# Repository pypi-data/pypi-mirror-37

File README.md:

# PyPI code 37

This repo contains 40000 packages uploaded to PyPI between 
2018-10-08 14:18 and 2018-11-02 07:18.

The repo is 100% (40000/40000) complete.

Package contents can be found [in the code branch](https://github.com/pypi-data/pypi-mirror-37/tree/code/packages).

A browsable package list for all repositories [all packages here](https://pypi-data.github.io/website/repositories/pypi-mirror-37).

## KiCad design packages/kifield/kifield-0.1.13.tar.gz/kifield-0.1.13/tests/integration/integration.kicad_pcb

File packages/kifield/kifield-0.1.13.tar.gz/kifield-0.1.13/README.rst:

===============================
kifield
===============================

.. image:: https://img.shields.io/pypi/v/kifield.svg
        :target: https://pypi.python.org/pypi/kifield
.. image:: https://travis-ci.org/xesscorp/KiField.svg?branch=master
    :target: https://travis-ci.org/xesscorp/KiField

A utility for manipulating part fields in KiCad schematic files or libraries.
KiField can extract all the component fields from a schematic or library
and place them into a spreadsheet for bulk editing, after which you can insert the
edited values from the spreadsheet back into the schematic or library.

KiField is usually employed in a three-step process:

#. First use KiField to extract the part field labels and values from a
   schematic or library and place them into a CSV or XLSX spreadsheet file.

#. Edit the spreadsheet file to change existing field values, add entirely
   new fields, or completely delete fields.

#. Finally, use KiField to insert the updated field labels and values from
   the spreadsheet file into the schematic or library.

* Free software: MIT license
* Documentation: https://xesscorp.github.io/KiField.

Features
--------

* Extracts all fields and values from one or more KiCad schematic libraries or files
  (even hierarchical designs), and inserts them into a spreadsheet (either
  CSV or XLSX format).
* Extracts all fields and values from one or more CSV or XLSX spreadsheet files
  and inserts them into one or more KiCad schematics or libraries.

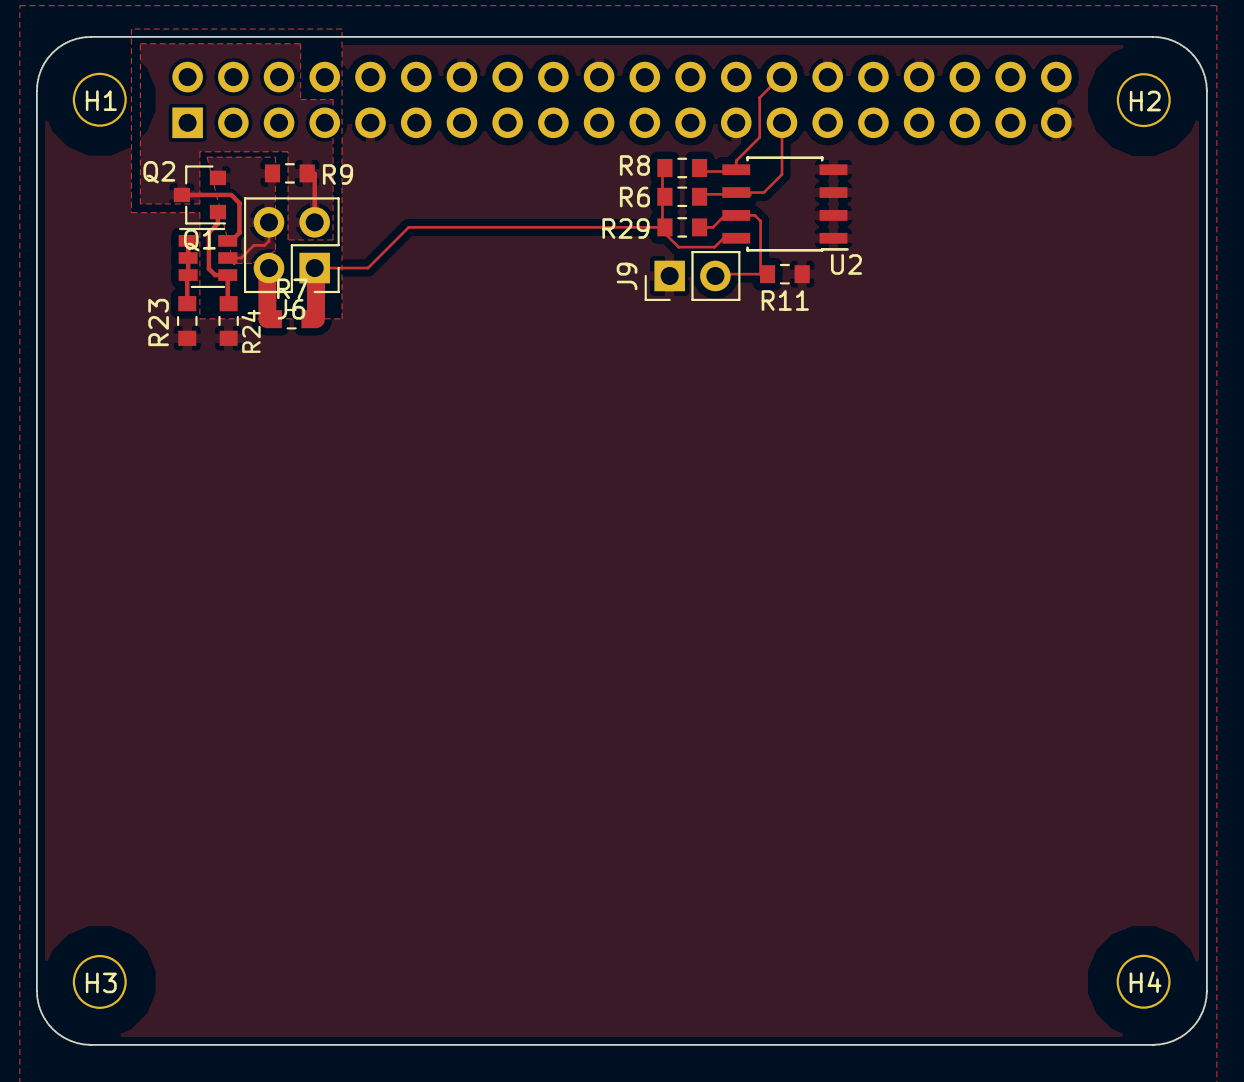
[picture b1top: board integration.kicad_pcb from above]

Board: 4 copper layers, 65.0 x 56.0 mm, 18 parts (1 on the bottom side), 10 nets.

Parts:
H1, H2, H3, H4: 3mm_Mounting_Hole; NPTH_3mm_ID
J3: 40HAT; PinSocket_2x20_P2.54mm_Vertical
J6: CONN_02X02; PinHeader_2x02_P2.54mm_Vertical
J9: CONN_01X02; PinHeader_1x02_P2.54mm_Vertical
Q1: DMG2305UX; SOT-23
Q2: DMMT5401; SOT-23-6
R6, R8: 3.9K; R_0603_1608Metric_Pad0.84x1.00mm_HandSolder
R7, R9, R11: DNP; R_0603_1608Metric_Pad0.84x1.00mm_HandSolder
R23, R24: 22; R_0603_1608Metric_Pad0.84x1.00mm_HandSolder
R29: 10K; R_0603_1608Metric_Pad0.84x1.00mm_HandSolder
U2: CAT24C32; SOIC-8_3.9x4.9mm_P1.27mm

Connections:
/ID_SC_EEPROM: J3.28, R8.2, U2.5
/ID_SD_EEPROM: J3.27, R6.2, U2.6
/P3V3: J6.1, R6.1, R7.2, R8.1, R29.1, U2.8
/P3V3_HAT: J3.1, J6.2, R7.1
/P5V: J6.3, Q1.3, Q2.6, R9.2
/P5V_HAT: J3.2, J3.4, J6.4, Q1.2, Q2.5, R9.1
GND: J3.6, J3.9, J3.14, J3.20, J3.25, J3.30, J3.34, J3.39, J9.1, R11.2, R23.2, R24.2, U2.1, U2.2, U2.3, U2.4
unnamed: J9.2, R11.1, R29.2, U2.7
unnamed: Q1.1, Q2.4, R24.1
unnamed: Q2.1, Q2.2, Q2.3, R23.1

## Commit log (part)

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2023-08-06 Add package mwparserfromhell/0.5.2/mwparserfromhell-0.5.2-cp34-cp34m-win_amd64.whl
2023-08-06 Add package midtransclient/1.0.4/midtransclient-1.0.4.tar.gz
2023-08-06 Add package mwparserfromhell/0.5.2/mwparserfromhell-0.5.2.tar.gz
2023-08-06 Add package sqlbag/0.1.1541129705/sqlbag-0.1.1541129705-py2.py3-none-any.whl
2023-08-06 Add package midtransclient/1.0.5/midtransclient-1.0.5-py2-none-any.whl
2023-08-06 Add package pykvf/0.1.12/pykvf-0.1.12.tar.gz
2023-08-06 Add package solarmax-ardexa/1.0.0/solarmax_ardexa-1.0.0-py2.py3-none-any.whl
2023-08-06 Add package mwparserfromhell/0.5.2/mwparserfromhell-0.5.2-cp37-cp37m-win_amd64.whl
2023-08-06 Add package mwparserfromhell/0.5.2/mwparserfromhell-0.5.2-cp36-cp36m-win_amd64.whl
2023-08-06 Add package antinex-utils/1.2.3/antinex-utils-1.2.3.tar.gz
2023-08-06 Add package flag-slurper/0.6.1/flag_slurper-0.6.1-py3-none-any.whl
2023-08-06 Add package stock-analysis-engine/1.1.29/stock-analysis-engine-1.1.29.tar.gz
2023-08-06 Add package docser/0.0.2/docser-0.0.2.tar.gz
2023-08-06 Add package antinex-client/1.3.5/antinex_client-1.3.5-py2.py3-none-any.whl
2023-08-06 Add package cateye/0.1.5/cateye-0.1.5.tar.gz
2023-08-06 Add package network-pipeline/1.2.10/network-pipeline-1.2.10.tar.gz
2023-08-06 Add package py-aiger-bdd/0.0.0/py-aiger-bdd-0.0.0.tar.gz
2023-08-06 Add package chatqhelper/1.1.6/chatqhelper-1.1.6.tar.gz
2023-08-06 Add package odoo11-addon-remote-report-to-printer/11.0.2.1.0.99.dev2/odoo11_addon_remote_report_to_printer-11.0.2.1.0.99.dev2-py2.py3-none-any.whl
2023-08-06 Add package aliyun-python-sdk-lubancloud/1.0.0/aliyun-python-sdk-lubancloud-1.0.0.tar.gz
2023-08-06 Add package rockhound/0.0.1/rockhound-0.0.1.tar.gz
2023-08-06 Add package odoo11-addons-oca-contract/11.0.20181101.0/odoo11_addons_oca_contract-11.0.20181101.0-py2.py3-none-any.whl
2023-08-06 Add package graph-cli/0.0.9/graph_cli-0.0.9.tar.gz
2023-08-06 Add package odoo11-addon-l10n-it-rea/11.0.1.0.0.99.dev3/odoo11_addon_l10n_it_rea-11.0.1.0.0.99.dev3-py2.py3-none-any.whl
2023-08-06 Add package odoo11-addon-agreement/11.0.0.0.1.99.dev17/odoo11_addon_agreement-11.0.0.0.1.99.dev17-py2.py3-none-any.whl
2023-08-06 Add package Wikked/0.8.0/Wikked-0.8.0.tar.gz
2023-08-06 Add package onelogin-aws-cli/0.1.16/onelogin_aws_cli-0.1.16.tar.gz
2023-08-06 Add package odoo11-addons-oca-report-print-send/11.0.20181101.0/odoo11_addons_oca_report_print_send-11.0.20181101.0-py2.py3-none-any.whl
2023-08-06 Add package genomelink/0.3.0/genomelink-0.3.0.tar.gz
2023-08-06 Add package pymagnitude/0.1.70/pymagnitude-0.1.70.tar.gz
2023-08-06 Add package paragami/0.1/paragami-0.1-py3-none-any.whl
2023-08-06 Add package plone.namedfile/5.0/plone.namedfile-5.0.tar.gz
2023-08-06 Add package ThreatPlaybook/1.2a11/ThreatPlaybook-1.2a11.tar.gz
2023-08-06 Add package metabot/0.0.1.2/metabot-0.0.1.2-py2.py3-none-any.whl
2023-08-06 Add package ThreatPlaybook/1.2a10/ThreatPlaybook-1.2a10.tar.gz
2023-08-06 Add package faster/0.1.4/faster-0.1.4-py2-none-any.whl
2023-08-06 Add package plone.outputfilters/3.1.0/plone.outputfilters-3.1.0.tar.gz
2023-08-06 Add package icetea/1.1.0rc1/icetea-1.1.0rc1.tar.gz
2023-08-06 Add package tronapi/2.0.3/tronapi-2.0.3.tar.gz
2023-08-06 Add package faster/0.1.6/faster-0.1.6-py2-none-any.whl
2023-08-06 Add package user-sdk/0.0.9/user-sdk-0.0.9.tar.gz
2023-08-06 Add package user-sdk/0.0.9/user_sdk-0.0.9-py3-none-any.whl
2023-08-06 Add package plone.protect/4.1.0/plone.protect-4.1.0-py2-none-any.whl
2023-08-06 Add package mysqldb-rich/2.5/mysqldb-rich-2.5.tar.gz
2023-08-06 Add package faster/0.1.9/faster-0.1.9-py2-none-any.whl
2023-08-06 Add package faster/0.1.10/faster-0.1.10-py2-none-any.whl
2023-08-06 Add package faster/0.1.9/faster-0.1.9-py3-none-any.whl
2023-08-06 Add package PYLIQ/1.0.1/PYLIQ-1.0.1.tar.gz
2023-08-06 Add package swifter/0.260/swifter-0.260.tar.gz
2023-08-06 Add package nats-publish/0.1.2/nats_publish-0.1.2-py2-none-any.whl
2023-08-06 Add package icetea/1.1.0rc2/icetea-1.1.0rc2.tar.gz
2023-08-06 Add package archery/1.2.2/archery-1.2.2.tar.gz
2023-08-06 Add package text-classifier-kv/0.0.8/text_classifier_kv-0.0.8-py2.py3-none-any.whl
2023-08-06 Add package deepspeech/0.4.0a0/deepspeech-0.4.0a0-cp35-cp35m-linux_armv7l.whl
2023-08-06 Add package block-hosts/0.0.2/block_hosts-0.0.2-py2.py3-none-any.whl
2023-08-06 Add package mpc/0.0.3/mpc-0.0.3.tar.gz
2023-08-06 Add package robby/0.5.4/robby-0.5.4.tar.gz
2023-08-06 Add package cliff/2.14.0/cliff-2.14.0-py2.py3-none-any.whl
2023-08-06 Add package digole/0.0.1.14/digole-0.0.1.14.tar.gz
2023-08-06 Add package os-acc/0.2.0/os_acc-0.2.0-py2.py3-none-any.whl
2023-08-06 Add package fonttools/3.32.0/fonttools-3.32.0-py2.py3-none-any.whl
2023-08-06 Add package azblob/0.1/azblob-0.1.tar.gz
2023-08-06 Add package python-designateclient/2.11.0/python-designateclient-2.11.0.tar.gz
2023-08-06 Add package vaex-core/0.4.2/vaex-core-0.4.2.tar.gz
2023-08-06 Add package hatchbuck/1.0.16/hatchbuck-1.0.16.tar.gz
2023-08-06 Add package glance-store/0.27.0/glance_store-0.27.0.tar.gz
2023-08-06 Add package tmux-list-learner/0.0.2/tmux_list_learner-0.0.2-py3-none-any.whl
2023-08-06 Add package deepspeech/0.4.0a0/deepspeech-0.4.0a0-cp36-cp36m-manylinux1_x86_64.whl
2023-08-06 Add package django-dynamic-filenames/1.1.4/django-dynamic-filenames-1.1.4.tar.gz
2023-08-06 Add package gnosis-py/0.4.5/gnosis-py-0.4.5.tar.gz
2023-08-06 Add package django-grappelli/2.10.4/django-grappelli-2.10.4.tar.gz
2023-08-06 Add package fusspy/2.1.0/fusspy-2.1.0.tar.gz
2023-08-06 Add package which-fonts-support/1.3.0/which_fonts_support-1.3.0.macosx-10.13-x86_64.tar.gz
2023-08-06 Add package persistable/0.5.7/persistable-0.5.7.tar.gz
2023-08-06 Add package groupdocs-viewer-cloud/18.7.0/groupdocs_viewer_cloud-18.7.0-py3-none-any.whl
2023-08-06 Add package lalsuite/6.49.1.dev20181101/lalsuite-6.49.1.dev20181101-cp27-cp27m-macosx_10_11_x86_64.whl
2023-08-06 Add package lalsuite/6.49.1.dev20181101/lalsuite-6.49.1.dev20181101-cp27-cp27m-manylinux1_x86_64.whl
2023-08-06 Add package deepspeech-gpu/0.4.0a0/deepspeech_gpu-0.4.0a0-cp27-cp27m-manylinux1_x86_64.whl
2023-08-06 Add package lalsuite/6.49.1.dev20181101/lalsuite-6.49.1.dev20181101-cp35-cp35m-manylinux1_x86_64.whl
2023-08-06 Add package lalsuite/6.49.1.dev20181101/lalsuite-6.49.1.dev20181101-cp36-cp36m-manylinux1_x86_64.whl
2023-08-06 Add package lalsuite/6.49.1.dev20181101/lalsuite-6.49.1.dev20181101-cp37-cp37m-macosx_10_11_x86_64.whl
2023-08-06 Add package lalsuite/6.49.1.dev20181101/lalsuite-6.49.1.dev20181101-cp37-cp37m-manylinux1_x86_64.whl
2023-08-06 Add package python-glanceclient/2.14.0/python-glanceclient-2.14.0.tar.gz
2023-08-06 Add package pyagrum/0.13.3/pyAgrum-0.13.3-cp27-cp27m-macosx_10_6_x86_64.whl
2023-08-06 Add package stsci-rtd-theme/0.0.2/stsci_rtd_theme-0.0.2.tar.gz
2023-08-06 Add package pyagrum/0.13.3/pyAgrum-0.13.3-cp27-cp27m-manylinux1_x86_64.whl
2023-08-06 Add package pyagrum/0.13.3/pyAgrum-0.13.3-cp34-cp34m-manylinux1_i686.whl
2023-08-06 Add package pyagrum/0.13.3/pyAgrum-0.13.3-cp27-cp27mu-manylinux1_x86_64.whl
2023-08-06 Add package pyagrum/0.13.3/pyAgrum-0.13.3-cp34-cp34m-manylinux1_x86_64.whl
2023-08-06 Add package hvac/0.7.0/hvac-0.7.0-py2.py3-none-any.whl
2023-08-06 Add package pyagrum/0.13.3/pyAgrum-0.13.3-cp36-cp36m-macosx_10_7_x86_64.whl
2023-08-06 Add package pyagrum/0.13.3/pyAgrum-0.13.3-cp36-cp36m-win32.whl
2023-08-06 Add package pyagrum/0.13.3/pyAgrum-0.13.3-cp35-cp35m-win_amd64.whl
2023-08-06 Add package pyagrum/0.13.3/pyAgrum-0.13.3-cp37-cp37m-manylinux1_x86_64.whl
2023-08-06 Add package cognite-sdk/0.11.9/cognite-sdk-0.11.9.tar.gz
2023-08-06 Add package cognite-sdk/0.11.9/cognite_sdk-0.11.9-py3-none-any.whl
2023-08-06 Add package dogma/0.0.2/dogma-0.0.2-py3-none-any.whl
2023-08-06 Add package gxformat2/0.8.0/gxformat2-0.8.0-py2.7.egg
2023-08-06 Add package fasvaorm/0.1.2/fasvaorm-0.1.2-py3-none-any.whl
2023-08-06 Add package digole/0.0.1.15/digole-0.0.1.15.tar.gz
2023-08-06 Add package siskin/0.38.1/siskin-0.38.1.tar.gz
2023-08-06 Add package monero-agent/1.7.3/monero_agent-1.7.3.tar.gz
2023-08-06 Add package Django/2.1.3/Django-2.1.3.tar.gz
2023-08-06 Add package netpyne/0.8.3/netpyne-0.8.3-py2.py3-none-any.whl
2023-08-06 Add package giossync/0.0.1/giossync-0.0.1.tar.gz
2023-08-06 Add package giossync/0.0.1/giossync-0.0.1-py3-none-any.whl
2023-08-06 Add package midaxusers/2.0.20/midaxusers-2.0.20-py3-none-any.whl
2023-08-06 Add package breaker/2.0.1/breaker-2.0.1-py2-none-any.whl
2023-08-06 Add package mac-logs/0.0.0/mac-logs-0.0.0.tar.gz
2023-08-06 Add package dirhunt/0.6.0/dirhunt-0.6.0.tar.gz
2023-08-06 Add package intermod-library/0.1.0/intermod_library-0.1.0-py3-none-any.whl
2023-08-06 Add package pycrypt-samn/1.2.1/pycrypt-samn-1.2.1.tar.gz
2023-08-06 Add package marlo/0.0.1.dev21/marlo-0.0.1.dev21.tar.gz
2023-08-06 Add package websockets/7.0/websockets-7.0-cp34-cp34m-manylinux1_x86_64.whl
2023-08-06 Add package daemonctl/1.3.9/daemonctl-1.3.9.tar.gz
2023-08-06 Add package python-kyototycoon-ng/0.7.5/python-kyototycoon-ng-0.7.5.tar.gz
2023-08-06 Add package websockets/7.0/websockets-7.0-cp34-cp34m-manylinux1_i686.whl
2023-08-06 Add package pycrypt-samn/1.2.1/pycrypt_samn-1.2.1-py3-none-any.whl
2023-08-06 Add package ruamel.yaml/0.15.76/ruamel.yaml-0.15.76-cp27-cp27mu-manylinux1_x86_64.whl
2023-08-06 Add package ruamel.yaml/0.15.76/ruamel.yaml-0.15.76-cp34-cp34m-win_amd64.whl
2023-08-06 Add package websockets/7.0/websockets-7.0-cp36-cp36m-manylinux1_i686.whl
2023-08-06 Add package deepspeech-gpu/0.4.0a0/deepspeech_gpu-0.4.0a0-cp34-cp34m-manylinux1_x86_64.whl
2023-08-06 Add package ruamel.yaml/0.15.76/ruamel.yaml-0.15.76-cp27-cp27m-macosx_10_9_x86_64.whl
2023-08-06 Add package ruamel.yaml/0.15.76/ruamel.yaml-0.15.76-cp27-cp27m-manylinux1_x86_64.whl
2023-08-06 Add package ruamel.yaml/0.15.76/ruamel.yaml-0.15.76-cp34-cp34m-manylinux1_x86_64.whl
2023-08-06 Add package ruamel.yaml/0.15.76/ruamel.yaml-0.15.76-cp36-cp36m-win_amd64.whl
2023-08-06 Add package django-redisboard/4.0.0/django-redisboard-4.0.0.tar.gz
2023-08-06 Add package ruamel.yaml/0.15.76/ruamel.yaml-0.15.76-cp36-cp36m-win32.whl
2023-08-06 Add package ruamel.yaml/0.15.76/ruamel.yaml-0.15.76-cp37-cp37m-macosx_10_9_x86_64.whl
2023-08-06 Add package robby/0.5.5/robby-0.5.5-py2-none-any.whl
2023-08-06 Add package ruamel.yaml/0.15.76/ruamel.yaml-0.15.76-cp36-cp36m-manylinux1_x86_64.whl
2023-08-06 Add package ruamel.yaml/0.15.76/ruamel.yaml-0.15.76-cp37-cp37m-win_amd64.whl
2023-08-06 Add package ruamel.yaml/0.15.76/ruamel.yaml-0.15.76-cp35-cp35m-manylinux1_x86_64.whl
2023-08-06 Add package politico-civic-ap-loader/0.4.0/politico-civic-ap-loader-0.4.0.tar.gz
2023-08-06 Add package treelog/1.0b2/treelog-1.0b2.tar.gz
2023-08-06 Add package intermod-library/0.1.1/intermod-library-0.1.1.tar.gz
2023-08-06 Add package websockets/7.0/websockets-7.0-cp34-cp34m-win32.whl
2023-08-06 Add package python-commander/0.1.1/python_commander-0.1.1.linux-x86_64.tar.gz
2023-08-06 Add package websockets/7.0/websockets-7.0-cp37-cp37m-win32.whl
2023-08-06 Add package websockets/7.0/websockets-7.0-cp37-cp37m-win_amd64.whl
2023-08-06 Add package python-commander/0.1.1/python_commander-0.1.1-py3-none-any.whl
2023-08-06 Add package dash-core-components/0.36.0/dash_core_components-0.36.0.tar.gz
2023-08-06 Add package yamlchecker/0.1.4/yamlchecker-0.1.4.tar.gz
2023-08-06 Add package tap-hubspot/2.2.4/tap-hubspot-2.2.4.tar.gz
2023-08-06 Add package dpu-utils/0.1.18/dpu_utils-0.1.18-py2.py3-none-any.whl
2023-08-06 Add package pycrypt-samn/1.2.2/pycrypt-samn-1.2.2.tar.gz
2023-08-06 Add package flask-filer/0.0.1/flask_filer-0.0.1-py3.6.egg
2023-08-06 Add package iotile-build/2.6.14/iotile-build-2.6.14.tar.gz
2023-08-06 Add package backend.ai-manager/1.4.2/backend.ai-manager-1.4.2.tar.gz
2023-08-06 Add package midaxusers/2.0.21/midaxusers-2.0.21.tar.gz
2023-08-06 Add package websockets/7.0/websockets-7.0-cp37-cp37m-macosx_10_6_intel.whl
2023-08-06 Add package escale/0.7.8/escale-0.7.8-py2.py3-none-any.whl
2023-08-06 Add package deepspeech-gpu/0.4.0a0/deepspeech_gpu-0.4.0a0-cp37-cp37m-manylinux1_x86_64.whl
2023-08-06 Add changes
2023-08-06 Add package python-velbus/2.0.21/python_velbus-2.0.21-py3-none-any.whl
